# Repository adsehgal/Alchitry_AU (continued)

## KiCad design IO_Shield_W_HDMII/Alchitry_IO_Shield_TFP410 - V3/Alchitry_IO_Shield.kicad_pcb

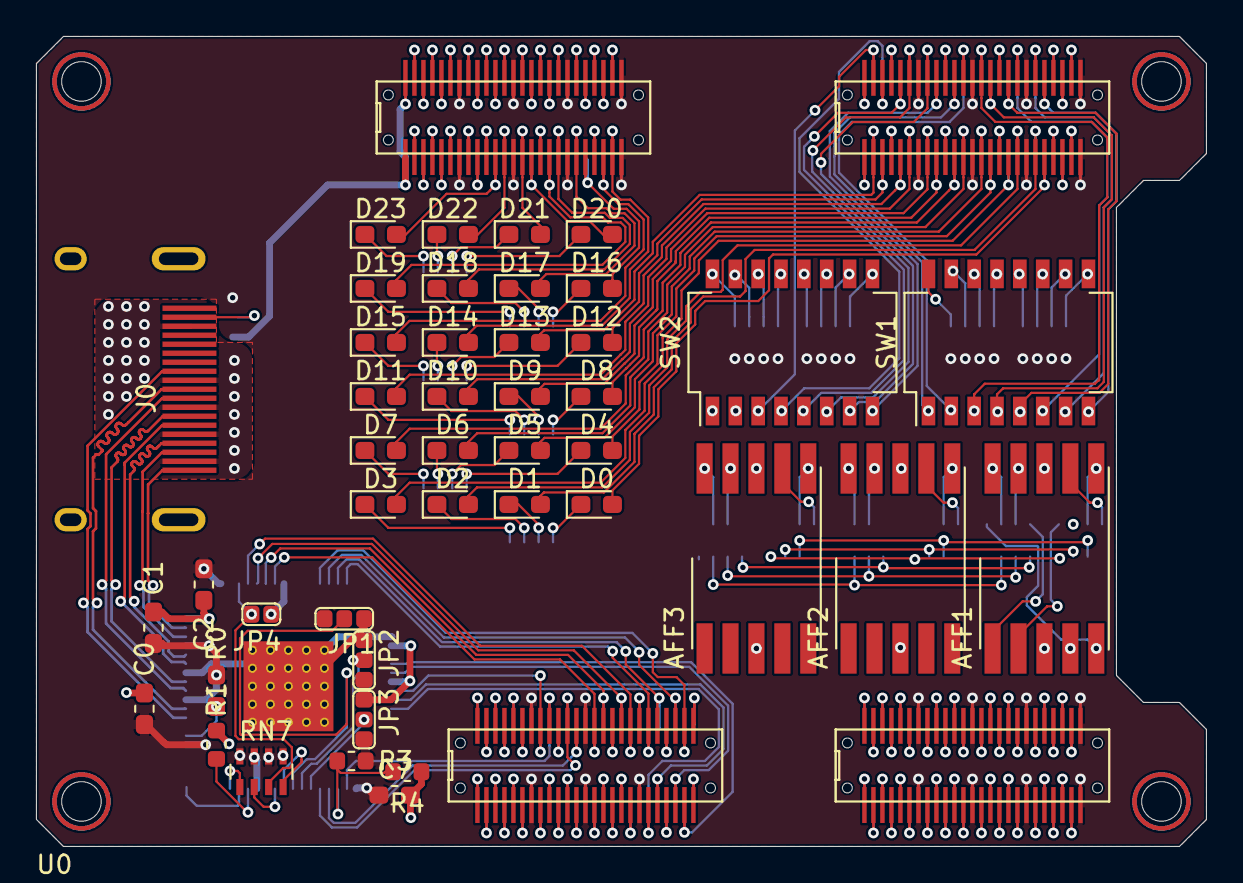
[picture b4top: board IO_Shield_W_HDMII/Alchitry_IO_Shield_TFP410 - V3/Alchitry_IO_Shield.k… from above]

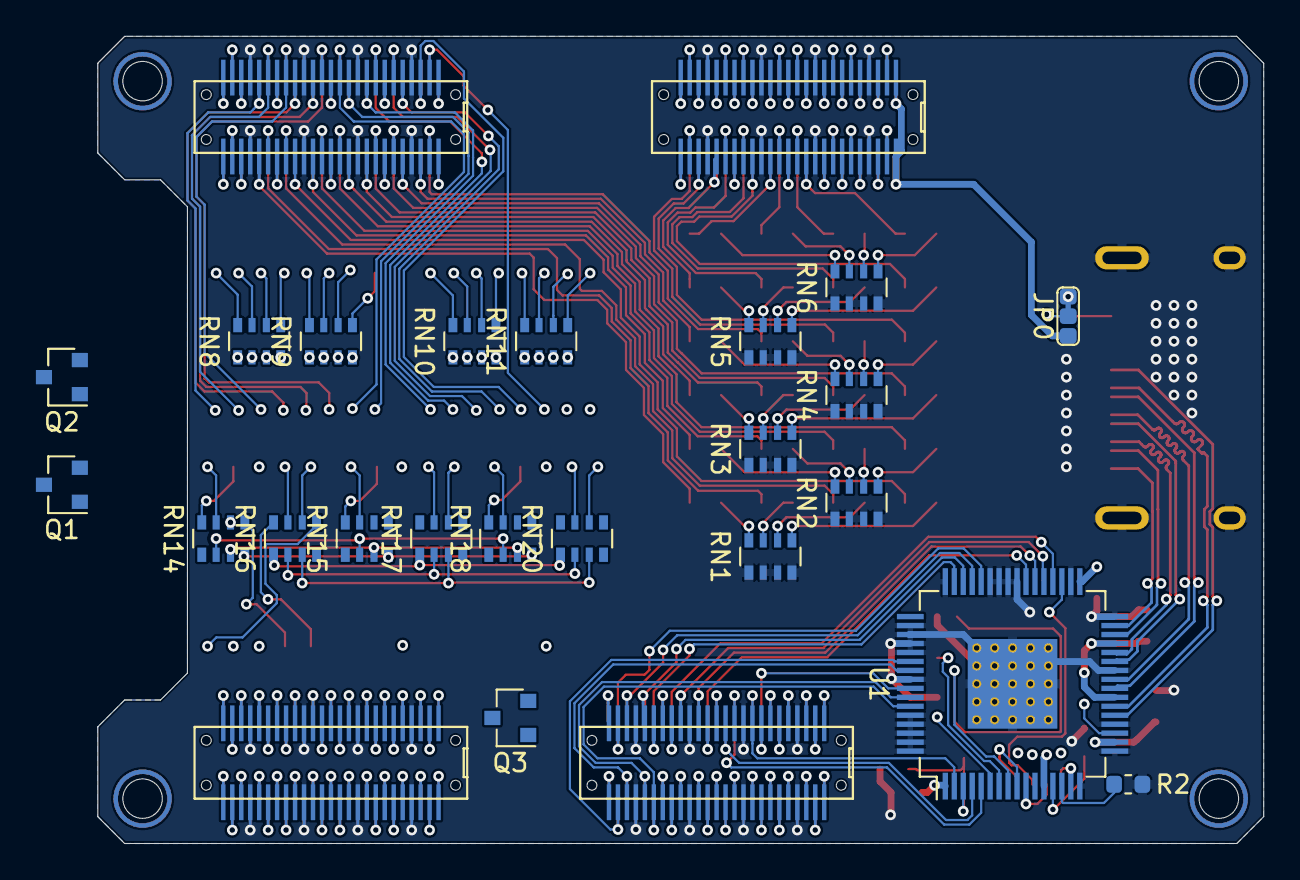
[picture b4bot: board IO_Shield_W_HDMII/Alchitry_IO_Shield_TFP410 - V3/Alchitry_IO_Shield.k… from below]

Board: 4 copper layers, 65.0 x 45.0 mm, 66 parts (22 on the bottom side), 228 nets.

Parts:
AFF1, AFF2, AFF3: LTS-6960HR; KCSC02-136
C0, C1, C2, C7: 100nF; C_0603_1608Metric_Pad1.05x0.95mm_HandSolder
D0, D1, D2, D3, D4, D5, D6, D7, D8, D9, D10, D11, D12, D13, D14, D15, D16, D17, D18, D19, D20, D21, D22, D23: LED; LED_0603_1608Metric_Pad1.05x0.95mm_HandSolder
J0: HDMI_A_1.4; HDMI
JP0: V_Sel; jumper_1_2_bridged
JP1: DK1; jumper_unbridged
JP2: DK2; jumper_unbridged
JP3: DK3; jumper_unbridged
JP4: DKEN; Jumper_2_Pin_Unbridged
Q1, Q2, Q3: Q_PMOS_SGD; SOT-23
R0: 510; R_0603_1608Metric_Pad1.05x0.95mm_HandSolder
R1, R2: 10K; R_0603_1608Metric
R3: 33K; R_0603_1608Metric
R4: 91K; R_0603_1608Metric
RN1, RN2, RN3, RN4, RN5, RN6, RN8, RN9, RN10, RN11, RN14, RN15, RN16, RN17, RN18, RN20: R_Pack04; R_Array_Convex_4x0603
RN7: 10K; R_Array_Concave_4x0603
SW1, SW2: SW_DIP_x08; SW_DIP_SPSTx08_Slide_Copal_CHS-08B_W7.62mm_P1.27mm
U0: boardmezzanine_new; Alchitry_Top_Bottom
U1: TFP410; HTQFP-64-1EP_10x10mm_P0.5mm_EP8x8mm_Mask4.4x4.4mm_ThermalVi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

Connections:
+3V3: C0.1, C1.1, C2.1, C7.1, JP0.1, JP1.1, JP2.1, JP3.1, Q1.3, Q2.3, Q3.3, R0.1, R3.2, RN7.1, RN7.2, RN7.3, RN7.4, RN8.1, RN8.2, RN8.3, RN8.4, RN9.1, RN9.2, RN9.3, RN9.4, RN10.1, RN10.2, RN10.3, RN10.4, RN11.1, RN11.2, RN11.3, RN11.4, U0.AB_7, U0.AB_13, U0.AB_19, U0.AB_25, U0.AB_26, U0.AB_32, U0.AB_38, U0.AB_44, U0.AT_7, U0.AT_13, U0.AT_19, U0.AT_25, U0.AT_26, U0.AT_32, U0.AT_38, U0.AT_44, U0.BB_7, U0.BB_13, U0.BB_19, U0.BB_25, U0.BB_26, U0.BB_32, U0.BB_38, U0.BB_44, U0.BT_7, U0.BT_13, U0.BT_19, U0.BT_25, U0.BT_26, U0.BT_32, U0.BT_38, U0.BT_44, U0.CB_7, U0.CB_13, U0.CB_19, U0.CB_38, U0.CB_44, U0.CT_7, U0.CT_13, U0.CT_19, U0.CT_38, U0.CT_44, U0.DB_7, U0.DB_13, U0.DB_19, U0.DB_25, U0.DB_26, U0.DB_32, U0.DB_38, U0.DB_44, U0.DT_7, U0.DT_13, U0.DT_19, U0.DT_25, U0.DT_26, U0.DT_32, U0.DT_38, U0.DT_44, U1.1, U1.12, U1.18, U1.23, U1.29, U1.33
+5V: JP0.3, U0.AB_1, U0.AB_50, U0.AT_1, U0.AT_50
/AN0: Q1.1, U0.AB_43, U0.AT_43
/AN1: Q2.1, U0.AB_42, U0.AT_42
/AN2: Q3.1, U0.AB_8, U0.AT_8
/AN3: U0.AB_9, U0.AT_9
/B0: U0.CB_20, U0.CT_20, U1.59
/B1: U0.CB_21, U0.CT_21, U1.58
/B2: U0.CB_23, U0.CT_23, U1.55
/B3: U0.CB_24, U0.CT_24, U1.54
/BTN0: U0.BB_28, U0.BT_28
/BTN1: U0.BB_27, U0.BT_27
/BTN2: U0.BB_23, U0.BT_23
/BTN3: U0.BB_24, U0.BT_24
/BTN4: U0.CB_49, U0.CT_49
/BTN5: U0.CB_48, U0.CT_48
/BTN6: U0.CB_46, U0.CT_46
/C0: RN14.1, RN15.1, RN18.1, U0.AB_5, U0.AT_5
/C1: RN14.2, RN15.2, RN18.2, U0.AB_6, U0.AT_6
/C2: RN14.3, RN15.3, RN18.3, U0.AB_48, U0.AT_48
/C3: RN14.4, RN15.4, RN18.4, U0.AB_46, U0.AT_46
/C4: RN16.1, RN17.1, RN20.1, U0.AB_45, U0.AT_45
/C5: RN16.2, RN17.2, RN20.2, U0.AB_3, U0.AT_3
/C6: RN16.3, RN17.3, RN20.3, U0.AB_2, U0.AT_2
/CLK: U0.CB_43, U0.CT_43, U1.57
/DE: U0.CB_42, U0.CT_42, U1.2
/DIP0: SW1.8, U0.BB_30, U0.BT_30
/DIP1: SW1.7, U0.BB_31, U0.BT_31
/DIP2: SW1.6, U0.BB_33, U0.BT_33
/DIP3: SW1.5, U0.BB_34, U0.BT_34
/DIP4: SW1.4, U0.BB_36, U0.BT_36
/DIP5: SW1.3, U0.BB_37, U0.BT_37
/DIP6: SW1.2, U0.BB_39, U0.BT_39
/DIP7: SW1.1, U0.BB_40, U0.BT_40
/DIP8: SW2.8, U0.BB_42, U0.BT_42
/DIP9: SW2.7, U0.BB_43, U0.BT_43
/DIP10: SW2.6, U0.BB_45, U0.BT_45
/DIP11: SW2.5, U0.BB_46, U0.BT_46
/DIP12: SW2.4, U0.BB_48, U0.BT_48
/DIP13: SW2.3, U0.BB_49, U0.BT_49
/DIP14: SW2.2, U0.AB_27, U0.AT_27
/DIP15: SW2.1, U0.AB_28, U0.AT_28
/DIP16: U0.AB_30, U0.AT_30
/DIP17: U0.AB_31, U0.AT_31
/DIP18: U0.AB_33, U0.AT_33
/DIP19: U0.AB_34, U0.AT_34
/DIP20: U0.AB_36, U0.AT_36
/DIP21: U0.AB_37, U0.AT_37
/DIP22: U0.AB_39, U0.AT_39
/DIP23: U0.AB_40, U0.AT_40
/DP: U0.AB_49, U0.AT_49
/G0: U0.CB_31, U0.CT_31, U1.47
/G1: U0.CB_30, U0.CT_30, U1.46
/G2: U0.CB_28, U0.CT_28, U1.45
/G3: U0.CB_27, U0.CT_27, U1.44
/HDMI/CK+: J0.10, U1.22
/HDMI/CK-: J0.12, U1.21
/HDMI/D0+: J0.7, U1.25
/HDMI/D0-: J0.9, U1.24
/HDMI/D1+: J0.4, U1.28
/HDMI/D1-: J0.6, U1.27
/HDMI/D2+: J0.1, U1.31
/HDMI/D2-: J0.3, U1.30
/HDMI/DK1: JP1.2, U1.8
/HDMI/DK2: JP2.2, U1.7
/HDMI/DK3: JP3.2, U1.6
/HDMI/ISEL: R1.1, U1.13
/HS: U0.CB_39, U0.CT_39, U1.4
/LED0: D0.2, U0.BB_21, U0.BT_21
/LED1: D1.2, U0.BB_20, U0.BT_20
/LED2: D2.2, U0.BB_18, U0.BT_18
/LED3: D3.2, U0.BB_17, U0.BT_17
/LED4: D4.2, U0.BB_15, U0.BT_15
/LED5: D5.2, U0.BB_14, U0.BT_14
/LED6: D6.2, U0.BB_12, U0.BT_12
/LED7: D7.2, U0.BB_11, U0.BT_11
/LED8: D8.2, U0.BB_9, U0.BT_9
/LED9: D9.2, U0.BB_8, U0.BT_8
/LED10: D10.2, U0.BB_6, U0.BT_6
/LED11: D11.2, U0.BB_5, U0.BT_5
/LED12: D12.2, U0.BB_3, U0.BT_3
/LED13: D13.2, U0.BB_2, U0.BT_2
/LED14: D14.2, U0.AB_24, U0.AT_24
/LED15: D15.2, U0.AB_23, U0.AT_23
/LED16: D16.2, U0.AB_21, U0.AT_21
/LED17: D17.2, U0.AB_20, U0.AT_20
/LED18: D18.2, U0.AB_18, U0.AT_18
/LED19: D19.2, U0.AB_17, U0.AT_17
/LED20: D20.2, U0.AB_15, U0.AT_15
/LED21: D21.2, U0.AB_14, U0.AT_14
/LED22: D22.2, U0.AB_12, U0.AT_12
/LED23: D23.2, U0.AB_11, U0.AT_11
/LEDs/DP: RN16.4, RN17.4, RN20.4
/R0: U0.CB_37, U0.CT_37, U1.39
/R1: U0.CB_36, U0.CT_36, U1.38
/R2: U0.CB_34, U0.CT_34, U1.37
/R3: U0.CB_33, U0.CT_33, U1.36
/VS: U0.CB_40, U0.CT_40, U1.5
GNDREF: C0.2, C1.2, C2.2, C7.2, J0.2, J0.5, J0.8, J0.11, J0.17, J0.SH, JP1.3, JP2.3, JP3.3, JP4.1, R1.2, R2.2, R4.2, RN1.1, RN1.2, RN1.3, RN1.4, RN2.1, RN2.2, RN2.3, RN2.4, RN3.1, RN3.2, RN3.3, RN3.4, RN4.1, RN4.2, RN4.3, RN4.4, RN5.1, RN5.2, RN5.3, RN5.4, RN6.1, RN6.2, RN6.3, RN6.4, U0.AB_4, U0.AB_10, U0.AB_16, U0.AB_22, U0.AB_29, U0.AB_35, U0.AB_41, U0.AB_47, U0.AT_4, U0.AT_10, U0.AT_16, U0.AT_22, U0.AT_29, U0.AT_35, U0.AT_41, U0.AT_47, U0.BB_4, U0.BB_10, U0.BB_16, U0.BB_22, U0.BB_29, U0.BB_35, U0.BB_41, U0.BB_47, U0.BT_4, U0.BT_10, U0.BT_16, U0.BT_22, U0.BT_29, U0.BT_35, U0.BT_41, U0.BT_47, U0.CB_4, U0.CB_10, U0.CB_16, U0.CB_22, U0.CB_29, U0.CB_35, U0.CB_41, U0.CB_47, U0.CT_4, U0.CT_10, U0.CT_16, U0.CT_22, U0.CT_29, U0.CT_35, U0.CT_41, U0.CT_47, U0.DB_4, U0.DB_10, U0.DB_16, U0.DB_22, U0.DB_29, U0.DB_35, U0.DB_41, U0.DB_47, U0.DT_4, U0.DT_10, U0.DT_16, U0.DT_22, U0.DT_29, U0.DT_35, U0.DT_41, U0.DT_47, U1.16, U1.17, U1.20, U1.26, U1.32, U1.34, U1.40, U1.41, U1.42, U1.43, U1.48, U1.50, U1.51, U1.52, U1.53, U1.56, U1.60, U1.61, U1.62, U1.63, U1.64, U1.65
unnamed: AFF1.1, RN16.8
unnamed: AFF1.2, RN14.5
unnamed: AFF1.3, AFF1.8, Q1.2
unnamed: AFF1.4, RN14.6
unnamed: AFF1.5, RN16.5
unnamed: AFF1.6, RN14.7
unnamed: AFF1.7, RN14.8
unnamed: AFF1.9, RN16.7
unnamed: AFF1.10, RN16.6
unnamed: AFF2.1, RN17.8
unnamed: AFF2.2, RN15.5
unnamed: AFF2.3, AFF2.8, Q2.2
unnamed: AFF2.4, RN15.6
unnamed: AFF2.5, RN17.5
unnamed: AFF2.6, RN15.7
unnamed: AFF2.7, RN15.8
unnamed: AFF2.9, RN17.7
unnamed: AFF2.10, RN17.6
unnamed: AFF3.1, RN20.8
unnamed: AFF3.2, RN18.5
unnamed: AFF3.3, AFF3.8, Q3.2
unnamed: AFF3.4, RN18.6
unnamed: AFF3.5, RN20.5
unnamed: AFF3.6, RN18.7
unnamed: AFF3.7, RN18.8
unnamed: AFF3.9, RN20.7
unnamed: AFF3.10, RN20.6
unnamed: D0.1, RN1.8
unnamed: D1.1, RN1.7
unnamed: D2.1, RN1.6
unnamed: D3.1, RN1.5
unnamed: D4.1, RN2.8
unnamed: D5.1, RN2.7
unnamed: D6.1, RN2.6
unnamed: D7.1, RN2.5
unnamed: D8.1, RN3.8
unnamed: D9.1, RN3.7
unnamed: D10.1, RN3.6
unnamed: D11.1, RN3.5
unnamed: D12.1, RN4.8
unnamed: D13.1, RN4.7
unnamed: D14.1, RN4.6
unnamed: D15.1, RN4.5
unnamed: D16.1, RN5.8
unnamed: D17.1, RN5.7
unnamed: D18.1, RN5.6
unnamed: D19.1, RN5.5
unnamed: D20.1, RN6.8
unnamed: D21.1, RN6.7
unnamed: D22.1, RN6.6
unnamed: D23.1, RN6.5
unnamed: J0.18, JP0.2
unnamed: JP4.2, RN7.7, U1.35
unnamed: R0.2, U1.19
unnamed: R2.1, U1.14
unnamed: R3.1, R4.1, U1.3
unnamed: RN7.5, U1.15
unnamed: RN7.6, U1.10
unnamed: RN7.8, U1.9
unnamed: RN8.5, SW1.12
unnamed: RN8.6, SW1.11
unnamed: RN8.7, SW1.10
unnamed: RN8.8, SW1.9
unnamed: RN9.5, SW1.16
unnamed: RN9.6, SW1.15
unnamed: RN9.7, SW1.14
unnamed: RN9.8, SW1.13
unnamed: RN10.5, SW2.12
unnamed: RN10.6, SW2.11
unnamed: RN10.7, SW2.10
unnamed: RN10.8, SW2.9
unnamed: RN11.5, SW2.16
unnamed: RN11.6, SW2.15
unnamed: RN11.7, SW2.14
unnamed: RN11.8, SW2.13
unnamed: U0.BB_1, U0.BT_1
unnamed: U0.BB_50, U0.BT_50
unnamed: U0.CB_1, U0.CT_1
unnamed: U0.CB_2, U0.CT_2
unnamed: U0.CB_3, U0.CT_3
unnamed: U0.CB_5, U0.CT_5
unnamed: U0.CB_6, U0.CT_6
unnamed: U0.CB_8, U0.CT_8
unnamed: U0.CB_9, U0.CT_9
unnamed: U0.CB_11, U0.CT_11
unnamed: U0.CB_12, U0.CT_12
unnamed: U0.CB_14, U0.CT_14
unnamed: U0.CB_15, U0.CT_15
unnamed: U0.CB_17, U0.CT_17
unnamed: U0.CB_18, U0.CT_18
unnamed: U0.CB_25, U0.CT_25
unnamed: U0.CB_26, U0.CT_26
unnamed: U0.CB_32, U0.CT_32
unnamed: U0.CB_45, U0.CT_45
unnamed: U0.CB_50, U0.CT_50
unnamed: U0.DB_1, U0.DT_1
unnamed: U0.DB_2, U0.DT_2
unnamed: U0.DB_3, U0.DT_3
unnamed: U0.DB_5, U0.DT_5
unnamed: U0.DB_6, U0.DT_6
unnamed: U0.DB_8, U0.DT_8
unnamed: U0.DB_9, U0.DT_9
unnamed: U0.DB_11, U0.DT_11
unnamed: U0.DB_12, U0.DT_12
unnamed: U0.DB_14, U0.DT_14
unnamed: U0.DB_15, U0.DT_15
unnamed: U0.DB_17, U0.DT_17
unnamed: U0.DB_18, U0.DT_18
unnamed: U0.DB_20, U0.DT_20
unnamed: U0.DB_21, U0.DT_21
unnamed: U0.DB_23, U0.DT_23
unnamed: U0.DB_24, U0.DT_24
unnamed: U0.DB_27, U0.DT_27
unnamed: U0.DB_28, U0.DT_28
unnamed: U0.DB_30, U0.DT_30
unnamed: U0.DB_31, U0.DT_31
unnamed: U0.DB_33, U0.DT_33
unnamed: U0.DB_34, U0.DT_34
unnamed: U0.DB_36, U0.DT_36
unnamed: U0.DB_37, U0.DT_37
unnamed: U0.DB_39, U0.DT_39
unnamed: U0.DB_40, U0.DT_40
unnamed: U0.DB_42, U0.DT_42
unnamed: U0.DB_43, U0.DT_43
unnamed: U0.DB_45, U0.DT_45
unnamed: U0.DB_46, U0.DT_46
unnamed: U0.DB_48, U0.DT_48
unnamed: U0.DB_49, U0.DT_49
unnamed: U0.DB_50, U0.DT_50

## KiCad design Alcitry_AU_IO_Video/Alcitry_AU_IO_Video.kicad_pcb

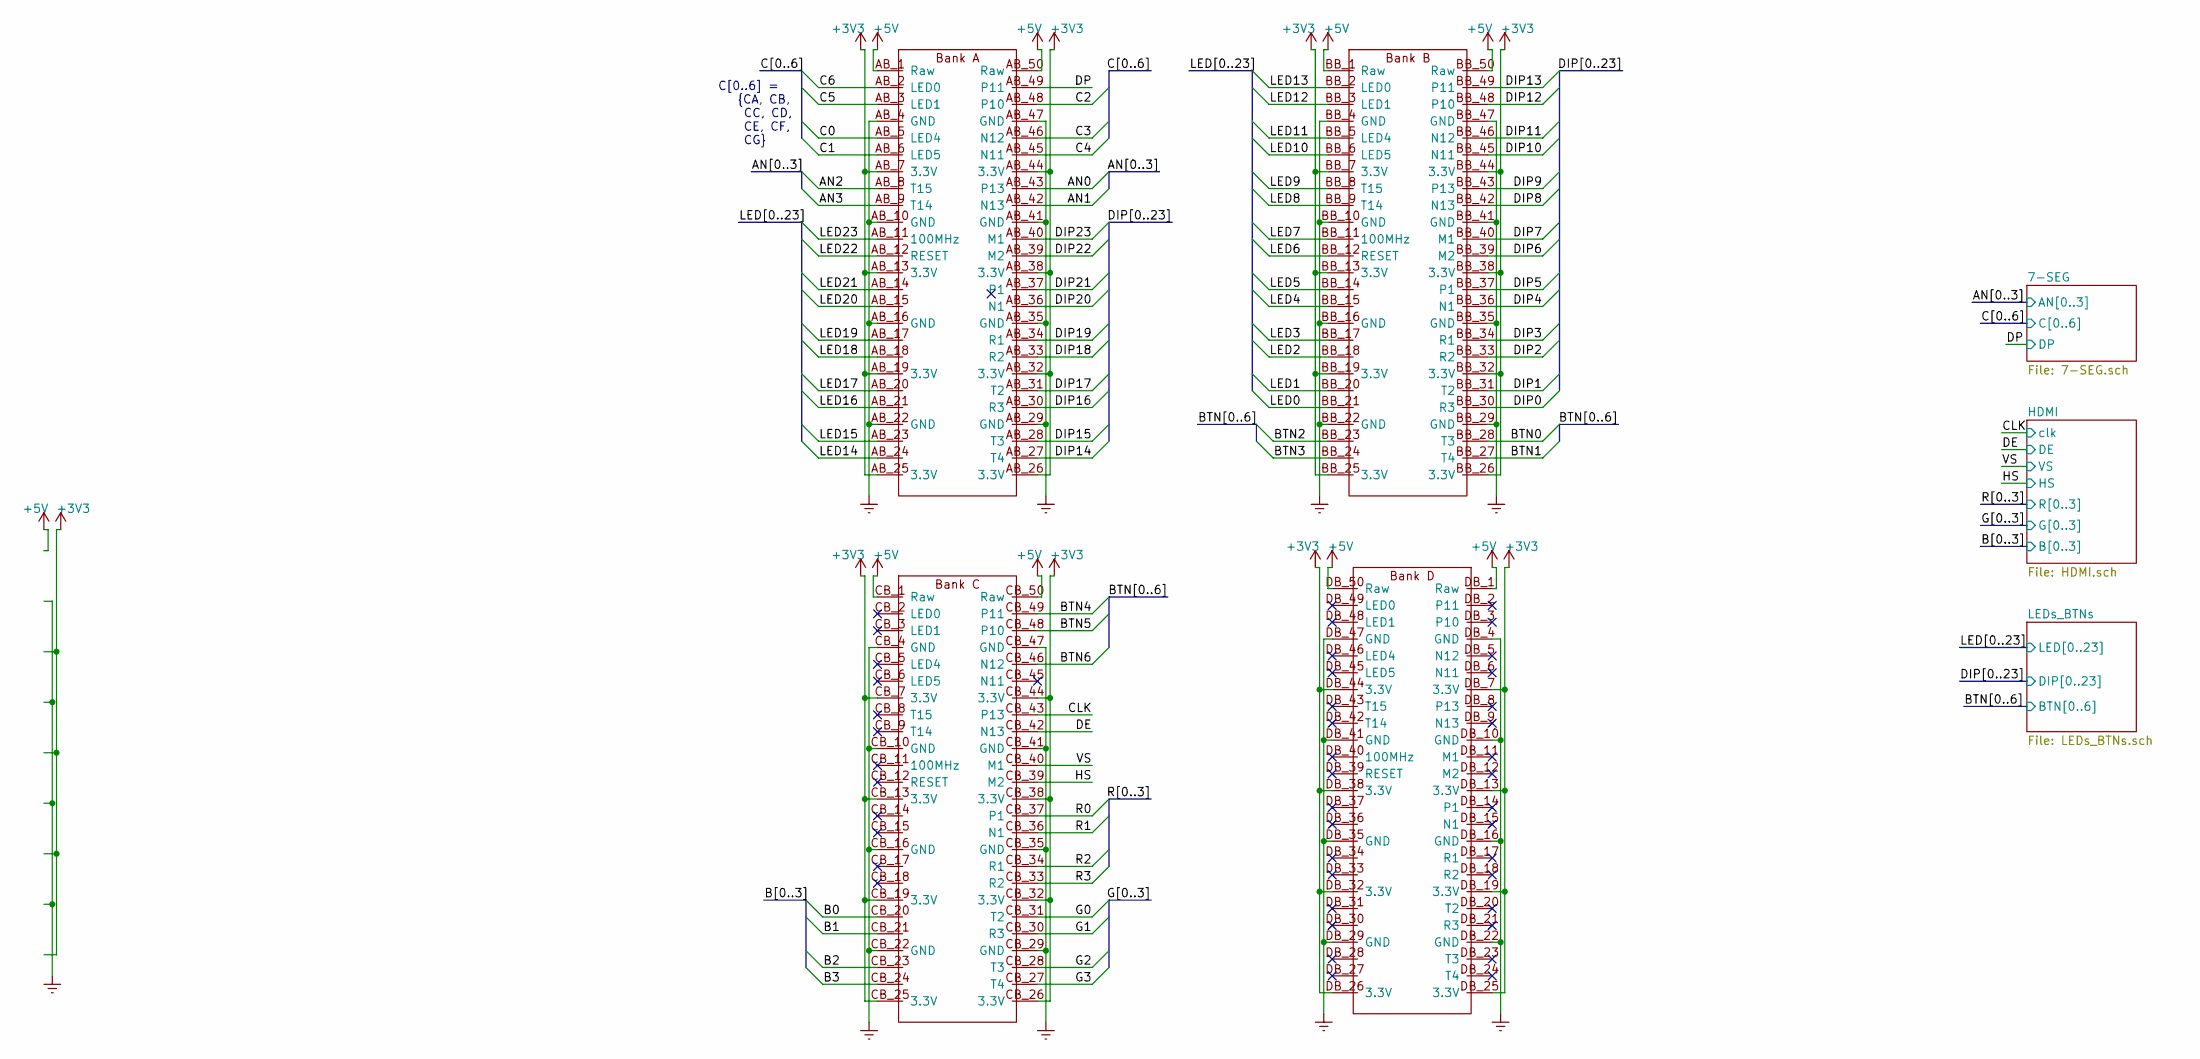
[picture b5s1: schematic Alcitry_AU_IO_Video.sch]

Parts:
U1: boardmezzanine_new; ELEMENT_NO_TOP

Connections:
+3V3: U1.AB_7 (3.3V), U1.AB_13 (3.3V), U1.AB_19 (3.3V), U1.AB_25 (3.3V), U1.AB_26 (3.3V), U1.AB_32 (3.3V), U1.AB_38 (3.3V), U1.AB_44 (3.3V), U1.BB_7 (3.3V), U1.BB_13 (3.3V), U1.BB_19 (3.3V), U1.BB_25 (3.3V), U1.BB_26 (3.3V), U1.BB_32 (3.3V), U1.BB_38 (3.3V), U1.BB_44 (3.3V), U1.CB_7 (3.3V), U1.CB_13 (3.3V), U1.CB_19 (3.3V), U1.CB_25 (3.3V), U1.CB_26 (3.3V), U1.CB_32 (3.3V), U1.CB_38 (3.3V), U1.CB_44 (3.3V), U1.DB_7 (3.3V), U1.DB_13 (3.3V), U1.DB_19 (3.3V), U1.DB_25 (3.3V), U1.DB_26 (3.3V), U1.DB_32 (3.3V), U1.DB_38 (3.3V), U1.DB_44 (3.3V); also elsewhere on the board
+5V: U1.AB_1 (Raw), U1.AB_50 (Raw), U1.BB_1 (Raw), U1.BB_50 (Raw), U1.CB_1 (Raw), U1.CB_50 (Raw), U1.DB_1 (Raw), U1.DB_50 (Raw); also elsewhere on the board
/AN0: U1.AB_43 (P13); also elsewhere on the board
/AN1: U1.AB_42 (N13); also elsewhere on the board
/AN2: U1.AB_8 (T15); also elsewhere on the board
/AN3: U1.AB_9 (T14); also elsewhere on the board
/B0: U1.CB_20; also elsewhere on the board
/B1: U1.CB_21; also elsewhere on the board
/B2: U1.CB_23; also elsewhere on the board
/B3: U1.CB_24; also elsewhere on the board
/BTN0: U1.BB_28 (T3); also elsewhere on the board
/BTN1: U1.BB_27 (T4); also elsewhere on the board
/BTN2: U1.BB_23; also elsewhere on the board
/BTN3: U1.BB_24; also elsewhere on the board
/BTN4: U1.CB_49 (P11); also elsewhere on the board
/BTN5: U1.CB_48 (P10); also elsewhere on the board
/BTN6: U1.CB_46 (N12); also elsewhere on the board
/C0: U1.AB_5 (LED4); also elsewhere on the board
/C1: U1.AB_6 (LED5); also elsewhere on the board
/C2: U1.AB_48 (P10); also elsewhere on the board
/C3: U1.AB_46 (N12); also elsewhere on the board
/C4: U1.AB_45 (N11); also elsewhere on the board
/C5: U1.AB_3 (LED1); also elsewhere on the board
/C6: U1.AB_2 (LED0); also elsewhere on the board
/CLK: U1.CB_43 (P13); also elsewhere on the board
/DE: U1.CB_42 (N13); also elsewhere on the board
/DIP0: U1.BB_30 (R3); also elsewhere on the board
/DIP1: U1.BB_31 (T2); also elsewhere on the board
/DIP2: U1.BB_33 (R2); also elsewhere on the board
/DIP3: U1.BB_34 (R1); also elsewhere on the board
/DIP4: U1.BB_36 (N1); also elsewhere on the board
/DIP5: U1.BB_37 (P1); also elsewhere on the board
/DIP6: U1.BB_39 (M2); also elsewhere on the board
/DIP7: U1.BB_40 (M1); also elsewhere on the board
/DIP8: U1.BB_42 (N13); also elsewhere on the board
/DIP9: U1.BB_43 (P13); also elsewhere on the board
/DIP10: U1.BB_45 (N11); also elsewhere on the board
/DIP11: U1.BB_46 (N12); also elsewhere on the board
/DIP12: U1.BB_48 (P10); also elsewhere on the board
/DIP13: U1.BB_49 (P11); also elsewhere on the board
/DIP14: U1.AB_27 (T4); also elsewhere on the board
/DIP15: U1.AB_28 (T3); also elsewhere on the board
/DIP16: U1.AB_30 (R3); also elsewhere on the board
/DIP17: U1.AB_31 (T2); also elsewhere on the board
/DIP18: U1.AB_33 (R2); also elsewhere on the board
/DIP19: U1.AB_34 (R1); also elsewhere on the board
/DIP20: U1.AB_36 (N1); also elsewhere on the board
/DIP21: U1.AB_37 (P1); also elsewhere on the board
/DIP22: U1.AB_39 (M2); also elsewhere on the board
/DIP23: U1.AB_40 (M1); also elsewhere on the board
/DP: U1.AB_49 (P11); also elsewhere on the board
/G0: U1.CB_31 (T2); also elsewhere on the board
/G1: U1.CB_30 (R3); also elsewhere on the board
/G2: U1.CB_28 (T3); also elsewhere on the board
/G3: U1.CB_27 (T4); also elsewhere on the board
/HS: U1.CB_39 (M2); also elsewhere on the board
/LED0: U1.BB_21; also elsewhere on the board
/LED1: U1.BB_20; also elsewhere on the board
/LED2: U1.BB_18; also elsewhere on the board
/LED3: U1.BB_17; also elsewhere on the board
/LED4: U1.BB_15; also elsewhere on the board
/LED5: U1.BB_14; also elsewhere on the board
/LED6: U1.BB_12 (RESET); also elsewhere on the board
/LED7: U1.BB_11 (100MHz); also elsewhere on the board
/LED8: U1.BB_9 (T14); also elsewhere on the board
/LED9: U1.BB_8 (T15); also elsewhere on the board
/LED10: U1.BB_6 (LED5); also elsewhere on the board
/LED11: U1.BB_5 (LED4); also elsewhere on the board
/LED12: U1.BB_3 (LED1); also elsewhere on the board
/LED13: U1.BB_2 (LED0); also elsewhere on the board
/LED14: U1.AB_24; also elsewhere on the board
/LED15: U1.AB_23; also elsewhere on the board
/LED16: U1.AB_21; also elsewhere on the board
/LED17: U1.AB_20; also elsewhere on the board
/LED18: U1.AB_18; also elsewhere on the board
/LED19: U1.AB_17; also elsewhere on the board
/LED20: U1.AB_15; also elsewhere on the board
/LED21: U1.AB_14; also elsewhere on the board
/LED22: U1.AB_12 (RESET); also elsewhere on the board
/LED23: U1.AB_11 (100MHz); also elsewhere on the board
/R0: U1.CB_37 (P1); also elsewhere on the board
/R1: U1.CB_36 (N1); also elsewhere on the board
/R2: U1.CB_34 (R1); also elsewhere on the board
/R3: U1.CB_33 (R2); also elsewhere on the board
/VS: U1.CB_40 (M1); also elsewhere on the board
GNDREF: U1.AB_4 (GND), U1.AB_10 (GND), U1.AB_16 (GND), U1.AB_22 (GND), U1.AB_29 (GND), U1.AB_35 (GND), U1.AB_41 (GND), U1.AB_47 (GND), U1.BB_4 (GND), U1.BB_10 (GND), U1.BB_16 (GND), U1.BB_22 (GND), U1.BB_29 (GND), U1.BB_35 (GND), U1.BB_41 (GND), U1.BB_47 (GND), U1.CB_4 (GND), U1.CB_10 (GND), U1.CB_16 (GND), U1.CB_22 (GND), U1.CB_29 (GND), U1.CB_35 (GND), U1.CB_41 (GND), U1.CB_47 (GND), U1.DB_4 (GND), U1.DB_10 (GND), U1.DB_16 (GND), U1.DB_22 (GND), U1.DB_29 (GND), U1.DB_35 (GND), U1.DB_41 (GND), U1.DB_47 (GND); also elsewhere on the board

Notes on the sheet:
C[0..6] = {CA, CB, CC, CD, CE, CF, CG}

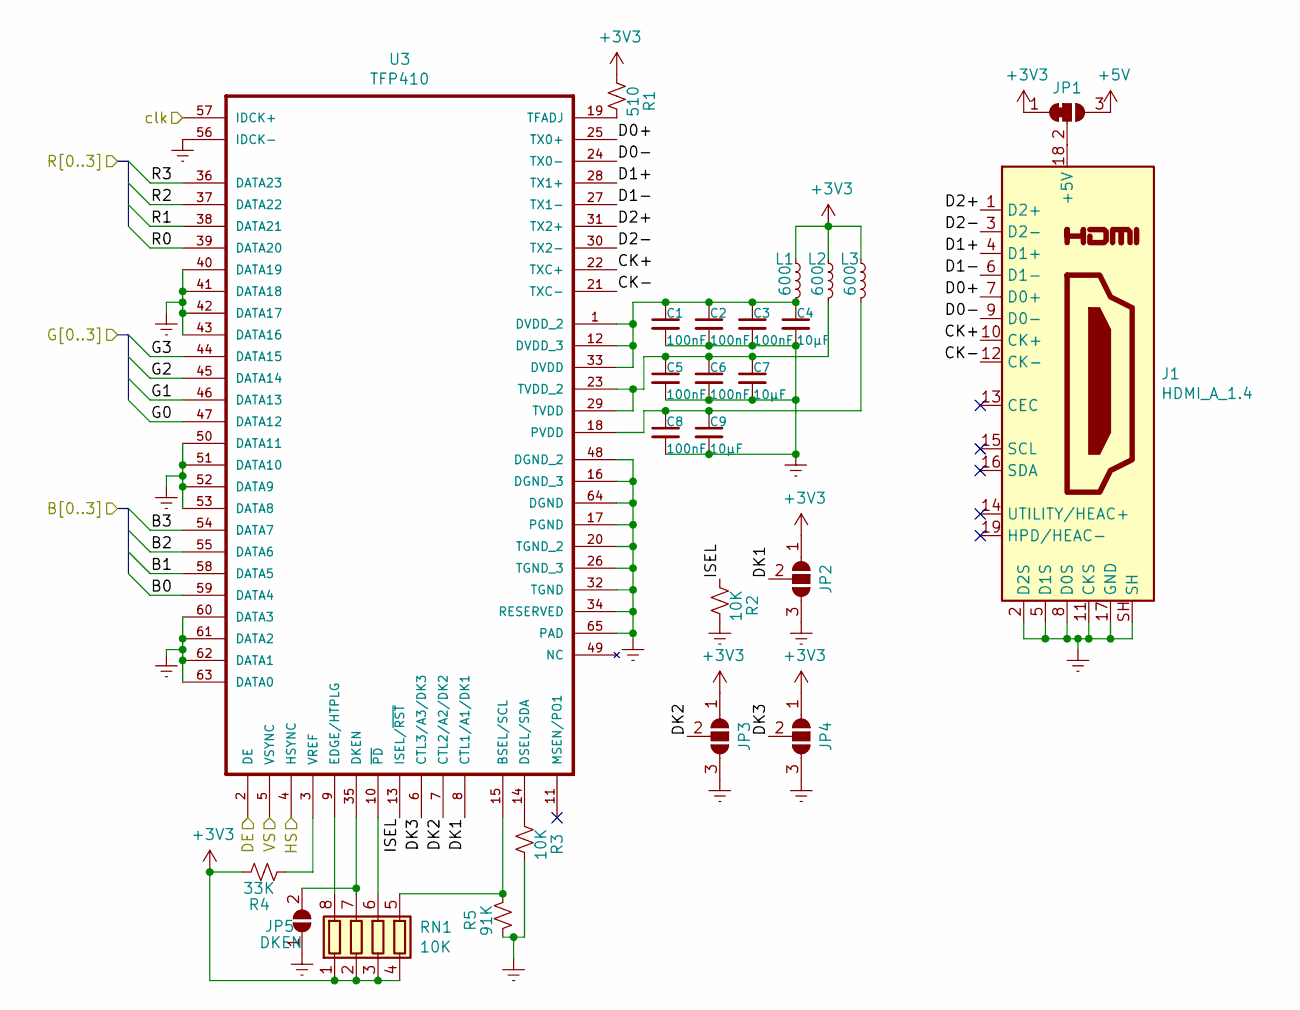
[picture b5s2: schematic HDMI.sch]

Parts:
C1, C2, C3, C5, C6, C8: 100nF; C_0603_1608Metric_Pad1.05x0.95mm_HandSolder
C4, C7, C9: 10µF; C_0603_1608Metric_Pad1.05x0.95mm_HandSolder
J1: HDMI_A_1.4; HDMI_Jing_C168714
JP1: V_Sel; SolderJumper-3_P1.3mm_Bridged12_RoundedPad1.0x1.5mm
JP2: DK1; SolderJumper-3_P1.3mm_Open_RoundedPad1.0x1.5mm
JP3: DK2; SolderJumper-3_P1.3mm_Open_RoundedPad1.0x1.5mm
JP4: DK3; SolderJumper-3_P1.3mm_Open_RoundedPad1.0x1.5mm
JP5: DKEN; SolderJumper-2_P1.3mm_Open_RoundedPad1.0x1.5mm
L1, L2, L3: 600; L_0603_1608Metric_Pad1.05x0.95mm_HandSolder
R1: 510; R_0603_1608Metric_Pad1.05x0.95mm_HandSolder
R2, R3: 10K; R_0603_1608Metric
R4: 33K; R_0603_1608Metric
R5: 91K; R_0603_1608Metric
RN1: 10K; R_Array_Concave_4x0603
U3: TFP410; HTQFP-64-1EP_10x10mm_P0.5mm_EP8x8mm_Mask4.4x4.4mm_ThermalVi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

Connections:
+3V3: JP1.1 (A), JP2.1 (A), JP3.1 (A), JP4.1 (A), L1.1, L2.1, L3.1, R1.1, R4.2, RN1.1 (R1.1), RN1.2 (R2.1), RN1.3 (R3.1), RN1.4 (R4.1); also elsewhere on the board
+5V: JP1.3 (B); also elsewhere on the board
/B0: U3.59 (DATA4); also elsewhere on the board
/B1: U3.58 (DATA5); also elsewhere on the board
/B2: U3.55 (DATA6); also elsewhere on the board
/B3: U3.54 (DATA7); also elsewhere on the board
/CLK: U3.57 (IDCK+); also elsewhere on the board
/DE: U3.2 (DE); also elsewhere on the board
/G0: U3.47 (DATA12); also elsewhere on the board
/G1: U3.46 (DATA13); also elsewhere on the board
/G2: U3.45 (DATA14); also elsewhere on the board
/G3: U3.44 (DATA15); also elsewhere on the board
/HDMI/CK+: J1.10 (CK+), U3.22 (TXC+)
/HDMI/CK-: J1.12 (CK-), U3.21 (TXC-)
/HDMI/D0+: J1.7 (D0+), U3.25 (TX0+)
/HDMI/D0-: J1.9 (D0-), U3.24 (TX0-)
/HDMI/D1+: J1.4 (D1+), U3.28 (TX1+)
/HDMI/D1-: J1.6 (D1-), U3.27 (TX1-)
/HDMI/D2+: J1.1 (D2+), U3.31 (TX2+)
/HDMI/D2-: J1.3 (D2-), U3.30 (TX2-)
/HDMI/DK1: JP2.2 (C), U3.8 (CTL1/A1/DK1)
/HDMI/DK2: JP3.2 (C), U3.7 (CTL2/A2/DK2)
/HDMI/DK3: JP4.2 (C), U3.6 (CTL3/A3/DK3)
/HDMI/ISEL: R2.1, U3.13 (ISEL/~RST)
/HS: U3.4 (HSYNC); also elsewhere on the board
/R0: U3.39 (DATA20); also elsewhere on the board
/R1: U3.38 (DATA21); also elsewhere on the board
/R2: U3.37 (DATA22); also elsewhere on the board
/R3: U3.36 (DATA23); also elsewhere on the board
/VS: U3.5 (VSYNC); also elsewhere on the board
GNDREF: C1.2, C2.2, C3.2, C4.2, C5.2, C6.2, C7.2, C8.2, C9.2, J1.2 (D2S), J1.5 (D1S), J1.8 (D0S), J1.11 (CKS), J1.17 (GND), J1.SH, JP2.3 (B), JP3.3 (B), JP4.3 (B), JP5.1 (A), R2.2, R3.2, R5.2, U3.16 (DGND_3), U3.17 (PGND), U3.20 (TGND_2), U3.26 (TGND_3), U3.32 (TGND), U3.34 (RESERVED), U3.40 (DATA19), U3.41 (DATA18), U3.42 (DATA17), U3.43 (DATA16), U3.48 (DGND_2), U3.50 (DATA11), U3.51 (DATA10), U3.52 (DATA9), U3.53 (DATA8), U3.56 (IDCK-), U3.60 (DATA3), U3.61 (DATA2), U3.62 (DATA1), U3.63 (DATA0), U3.64 (DGND), U3.65 (PAD); also elsewhere on the board
unnamed: C1.1, C2.1, C3.1, C4.1, L1.2, U3.1 (DVDD_2), U3.12 (DVDD_3), U3.33 (DVDD)
unnamed: C5.1, C6.1, C7.1, L2.2, U3.23 (TVDD_2), U3.29 (TVDD)
unnamed: C8.1, C9.1, L3.2, U3.18 (PVDD)
unnamed: J1.18 (+5V), JP1.2 (C)
unnamed: JP5.2 (B), RN1.7 (R2.2), U3.35 (DKEN)
unnamed: R1.2, U3.19 (TFADJ)
unnamed: R3.1, U3.14 (DSEL/SDA)
unnamed: R4.1, U3.3 (VREF)
unnamed: R5.1, RN1.5 (R4.2), U3.15 (BSEL/SCL)
unnamed: RN1.6 (R3.2), U3.10 (~PD)
unnamed: RN1.8 (R1.2), U3.9 (EDGE/HTPLG)

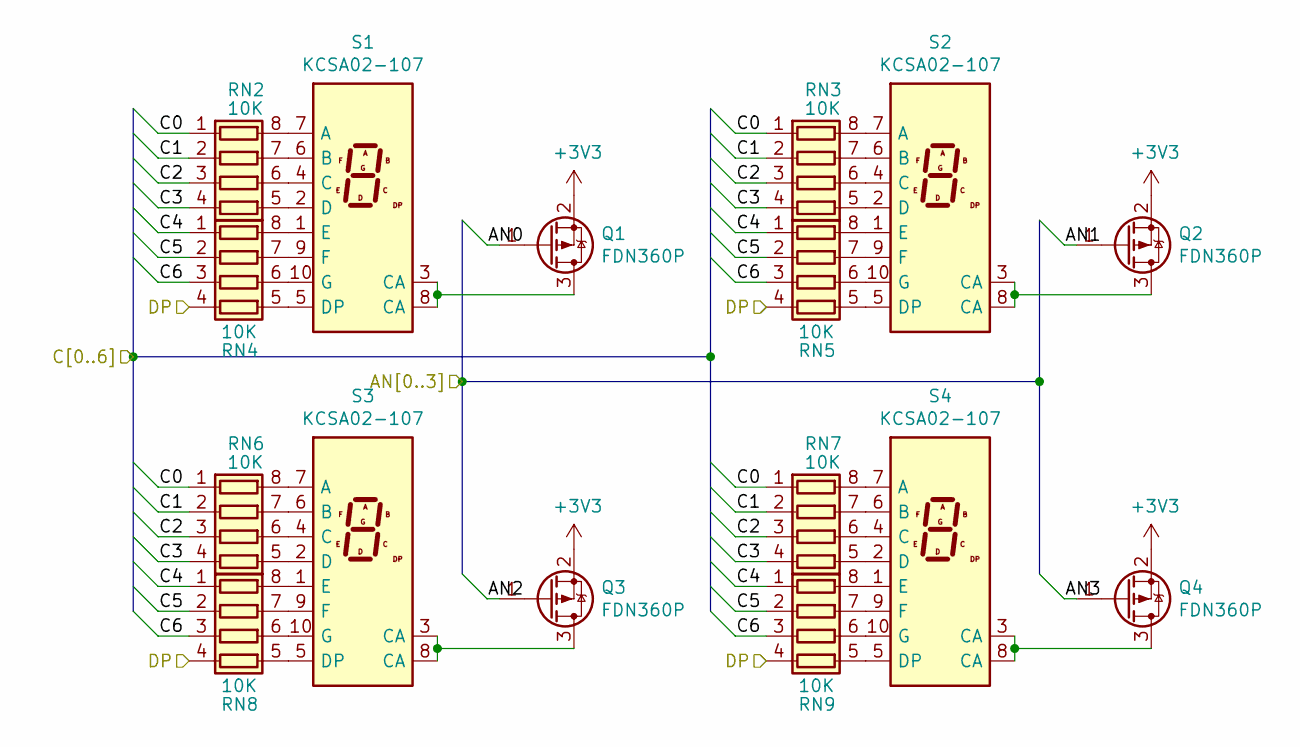
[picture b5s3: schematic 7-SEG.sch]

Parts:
Q1, Q2, Q3, Q4: FDN360P; SOT-23
RN2, RN3, RN4, RN5, RN6, RN7, RN8, RN9: 10K; R_Array_Concave_4x0603
S1, S2, S3, S4: KCSA02-107; KCSC02-105

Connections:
+3V3: Q1.2 (S), Q2.2 (S), Q3.2 (S), Q4.2 (S); also elsewhere on the board
/AN0: Q1.1 (G); also elsewhere on the board
/AN1: Q2.1 (G); also elsewhere on the board
/AN2: Q3.1 (G); also elsewhere on the board
/AN3: Q4.1 (G); also elsewhere on the board
/C0: RN2.1 (R1.1), RN3.1 (R1.1), RN6.1 (R1.1), RN7.1 (R1.1); also elsewhere on the board
/C1: RN2.2 (R2.1), RN3.2 (R2.1), RN6.2 (R2.1), RN7.2 (R2.1); also elsewhere on the board
/C2: RN2.3 (R3.1), RN3.3 (R3.1), RN6.3 (R3.1), RN7.3 (R3.1); also elsewhere on the board
/C3: RN2.4 (R4.1), RN3.4 (R4.1), RN6.4 (R4.1), RN7.4 (R4.1); also elsewhere on the board
/C4: RN4.1 (R1.1), RN5.1 (R1.1), RN8.1 (R1.1), RN9.1 (R1.1); also elsewhere on the board
/C5: RN4.2 (R2.1), RN5.2 (R2.1), RN8.2 (R2.1), RN9.2 (R2.1); also elsewhere on the board
/C6: RN4.3 (R3.1), RN5.3 (R3.1), RN8.3 (R3.1), RN9.3 (R3.1); also elsewhere on the board
/DP: RN4.4 (R4.1), RN5.4 (R4.1), RN8.4 (R4.1), RN9.4 (R4.1); also elsewhere on the board
unnamed: Q1.3 (D), S1.3 (CA), S1.8 (CA)
unnamed: Q2.3 (D), S2.3 (CA), S2.8 (CA)
unnamed: Q3.3 (D), S3.3 (CA), S3.8 (CA)
unnamed: Q4.3 (D), S4.3 (CA), S4.8 (CA)
unnamed: RN2.5 (R4.2), S1.2 (D)
unnamed: RN2.6 (R3.2), S1.4 (C)
unnamed: RN2.7 (R2.2), S1.6 (B)
unnamed: RN2.8 (R1.2), S1.7 (A)
unnamed: RN3.5 (R4.2), S2.2 (D)
unnamed: RN3.6 (R3.2), S2.4 (C)
unnamed: RN3.7 (R2.2), S2.6 (B)
unnamed: RN3.8 (R1.2), S2.7 (A)
unnamed: RN4.5 (R4.2), S1.5 (DP)
unnamed: RN4.6 (R3.2), S1.10 (G)
unnamed: RN4.7 (R2.2), S1.9 (F)
unnamed: RN4.8 (R1.2), S1.1 (E)
unnamed: RN5.5 (R4.2), S2.5 (DP)
unnamed: RN5.6 (R3.2), S2.10 (G)
unnamed: RN5.7 (R2.2), S2.9 (F)
unnamed: RN5.8 (R1.2), S2.1 (E)
unnamed: RN6.5 (R4.2), S3.2 (D)
unnamed: RN6.6 (R3.2), S3.4 (C)
unnamed: RN6.7 (R2.2), S3.6 (B)
unnamed: RN6.8 (R1.2), S3.7 (A)
unnamed: RN7.5 (R4.2), S4.2 (D)
unnamed: RN7.6 (R3.2), S4.4 (C)
unnamed: RN7.7 (R2.2), S4.6 (B)
unnamed: RN7.8 (R1.2), S4.7 (A)
unnamed: RN8.5 (R4.2), S3.5 (DP)
unnamed: RN8.6 (R3.2), S3.10 (G)
unnamed: RN8.7 (R2.2), S3.9 (F)
unnamed: RN8.8 (R1.2), S3.1 (E)
unnamed: RN9.5 (R4.2), S4.5 (DP)
unnamed: RN9.6 (R3.2), S4.10 (G)
unnamed: RN9.7 (R2.2), S4.9 (F)
unnamed: RN9.8 (R1.2), S4.1 (E)
